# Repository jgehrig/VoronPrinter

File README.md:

# VoronPrinter
Build Logs, Notes, and Design Modifications for a Voron 3D Printer

## Cura Slicer Setup
[Cura Slicer Configuration](config/cura)

## Extended Feet
[Extended Printer Feet](mods/extended_feet)

## Power Entry Connector
[Power Entry Connector MountPCB](mods/power_entry)

## Wiring PCB
[Wiring Helper PCB](mods/wiring_pcb)

## X Gantry Endstop
[Adjustable X Gantry Endstop](mods/x_gantry_endstop)

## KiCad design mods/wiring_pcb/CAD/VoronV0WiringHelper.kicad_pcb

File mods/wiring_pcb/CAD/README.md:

https://www.cui.com/product/resource/pcbfootprint/p783f-q24-s5-s

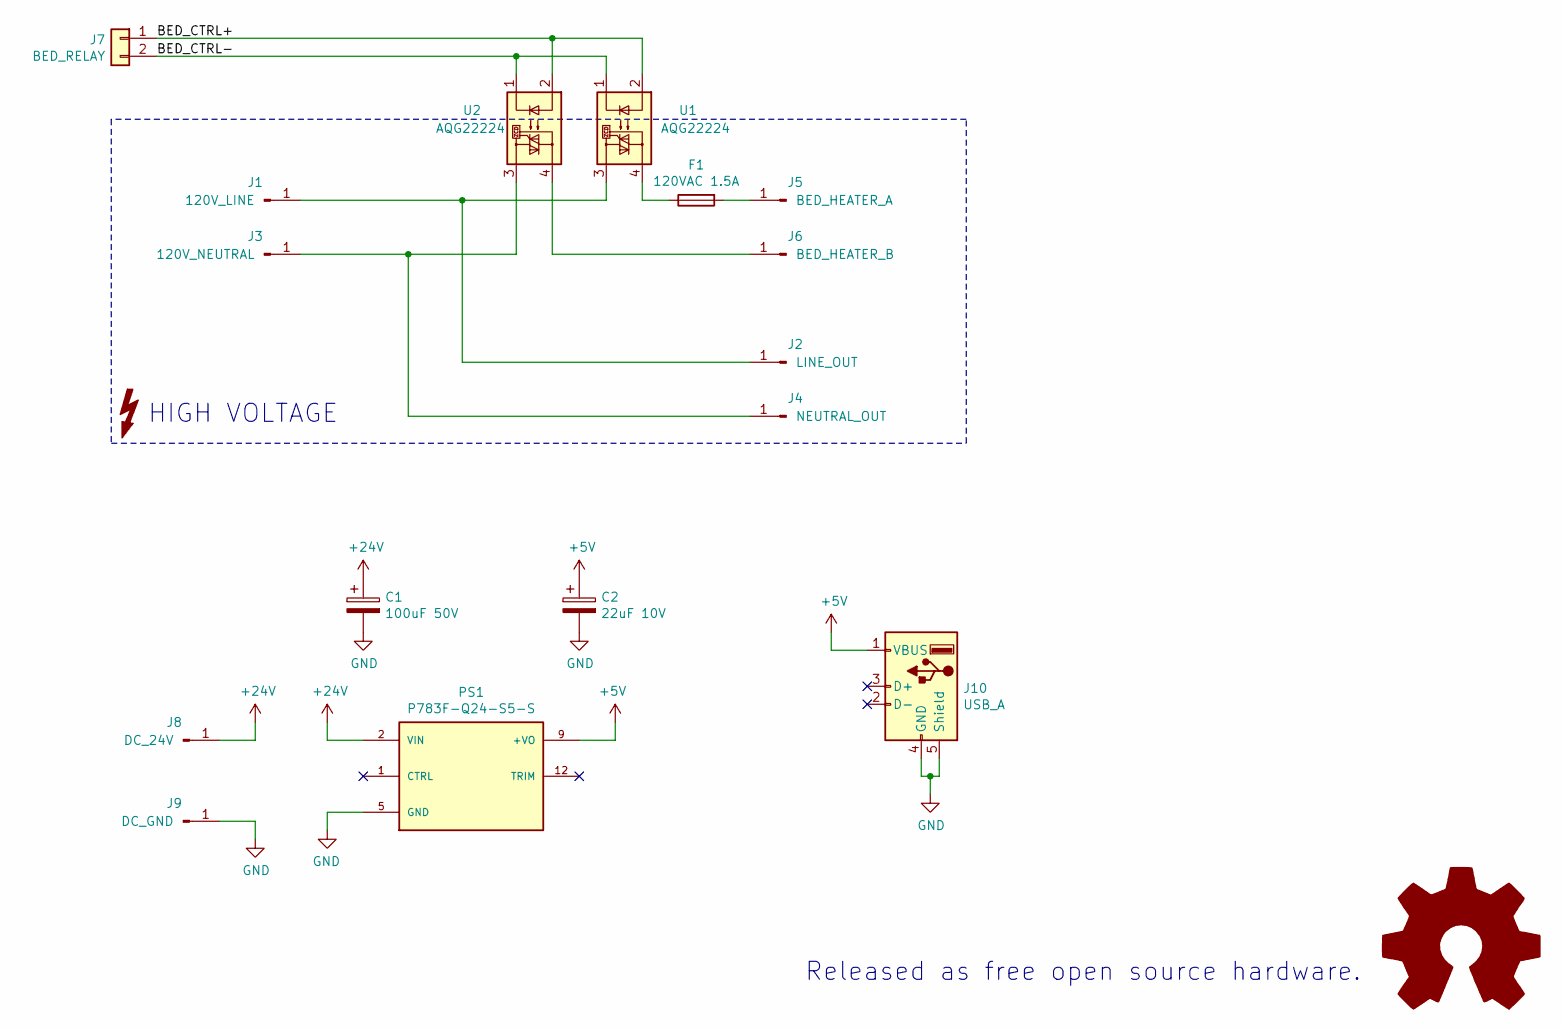
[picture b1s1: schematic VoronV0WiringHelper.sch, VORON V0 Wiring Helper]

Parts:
C1: 100uF 50V; CP_Radial_D8.0mm_P3.50mm
C2: 22uF 10V; CP_Radial_D5.0mm_P2.00mm
F1: 120VAC 1.5A; Fuseholder_Cylinder-5x20mm_Schurter_0031_8201_Horizontal_Op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
J1: 120V_LINE; CONN_63824-1
J2: LINE_OUT; CONN_63824-1
J3: 120V_NEUTRAL; CONN_63824-1
J4: NEUTRAL_OUT; CONN_63824-1
J5: BED_HEATER_A; CONN_63824-1
J6: BED_HEATER_B; CONN_63824-1
J7: BED_RELAY; JST_XH_B2B-XH-A_1x02_P2.50mm_Vertical
J8: DC_24V; CONN_63824-1
J9: DC_GND; CONN_63824-1
J10: USB_A; USB_A_CONNFLY_DS1095-WNR0
PS1: P783F-Q24-S5-S; CONV_P783F-Q24-S5-S; PARTREV 1.0
U1, U2: AQG22224

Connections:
+5V: C2.1, J10.1 (VBUS), PS1.9 (+VO), PS1.10 (+VO), PS1.11 (+VO)
+24V: C1.1, J8.1, PS1.2 (VIN), PS1.3 (VIN), PS1.4 (VIN)
/BED_CTRL+: J7.1, U1.2, U2.2
/BED_CTRL-: J7.2, U1.1, U2.1
GND: C1.2, C2.2, J9.1, J10.4 (GND), J10.5 (Shield), PS1.5 (GND), PS1.6 (GND), PS1.7 (GND), PS1.8 (GND)
unnamed: F1.1, U1.4
unnamed: F1.2, J5.1
unnamed: J1.1, J2.1, U1.3
unnamed: J3.1, J4.1, U2.3
unnamed: J6.1, U2.4

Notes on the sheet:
Released as free open source hardware.
HIGH VOLTAGE

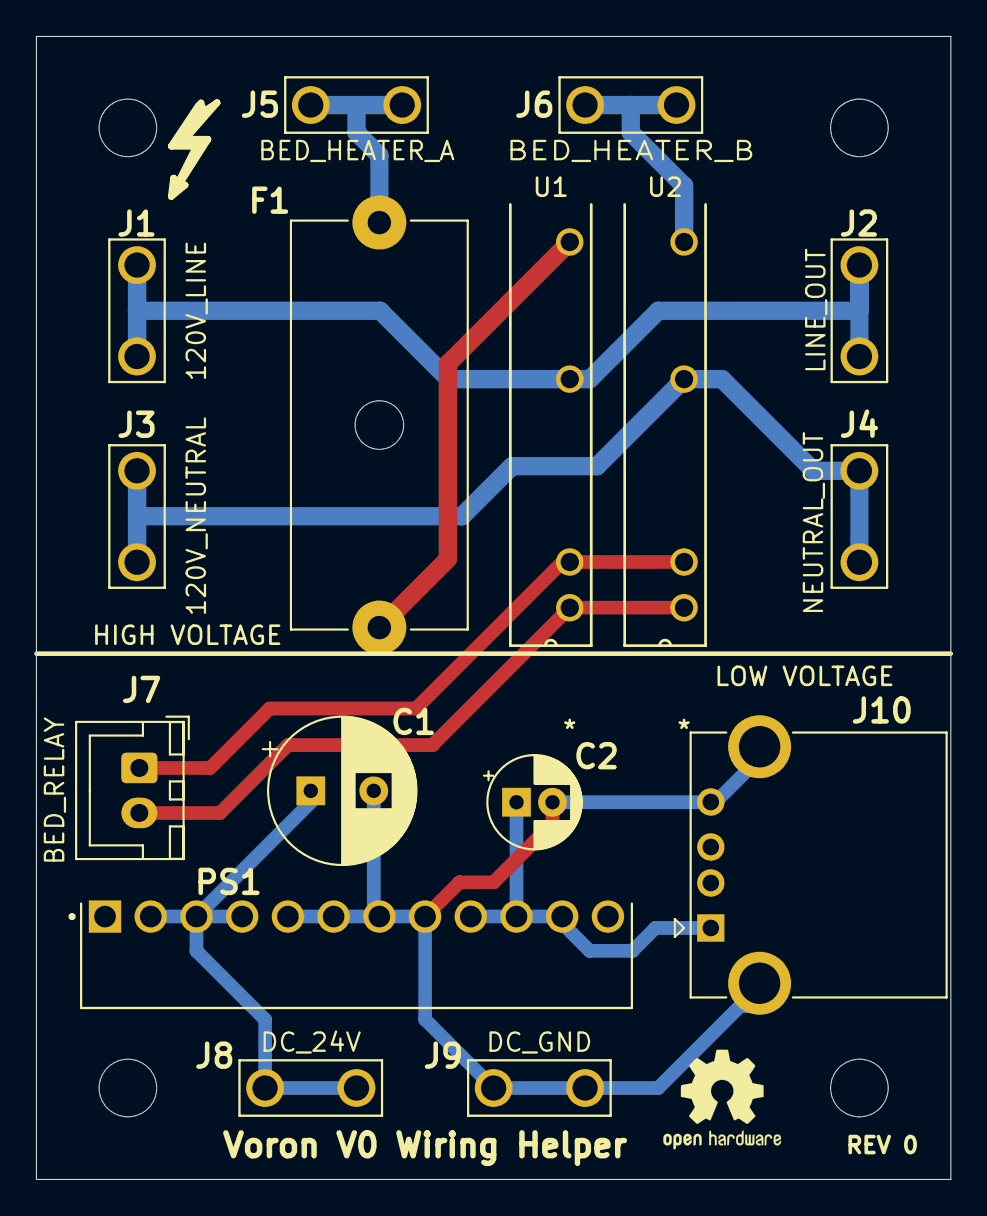
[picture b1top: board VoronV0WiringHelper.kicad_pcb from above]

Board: 2 copper layers, 50.8 x 63.5 mm, 16 parts (0 on the bottom side), 10 nets.

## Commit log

2021-03-12 Add X Gantry Endstop
2021-03-12 Add Power Entry Bracket
2021-03-12 Add Voron Wiring Helper PCB
2021-03-22 Add WiringHelper PCB image
    Update WiringHelper README, add image. Fixes table markdown.
2021-04-16 Add Extended Feet Mod
    This mod contains feet with additional space, and keying to the 1515
    extrusions. These feet were necessary to accommodate my wiring.
2021-04-16 Add Cura Configuration Instruction
    Instructions for setting up Cura for use with a generic Voron V0
    Printer. Tested on Linux with Cura 4.8.

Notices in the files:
parts and their libraries:
Copyright 2016 Accelerated Designs. All rights reserved.
